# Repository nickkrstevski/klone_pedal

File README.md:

# klone_pedal

Overdrive guitar pedal

Created by Nicholas Krstevski <nick@atopile.com>

# Assembly BOM Table
| Description | Link |
|-------------|-------------|
| Audio Jack |

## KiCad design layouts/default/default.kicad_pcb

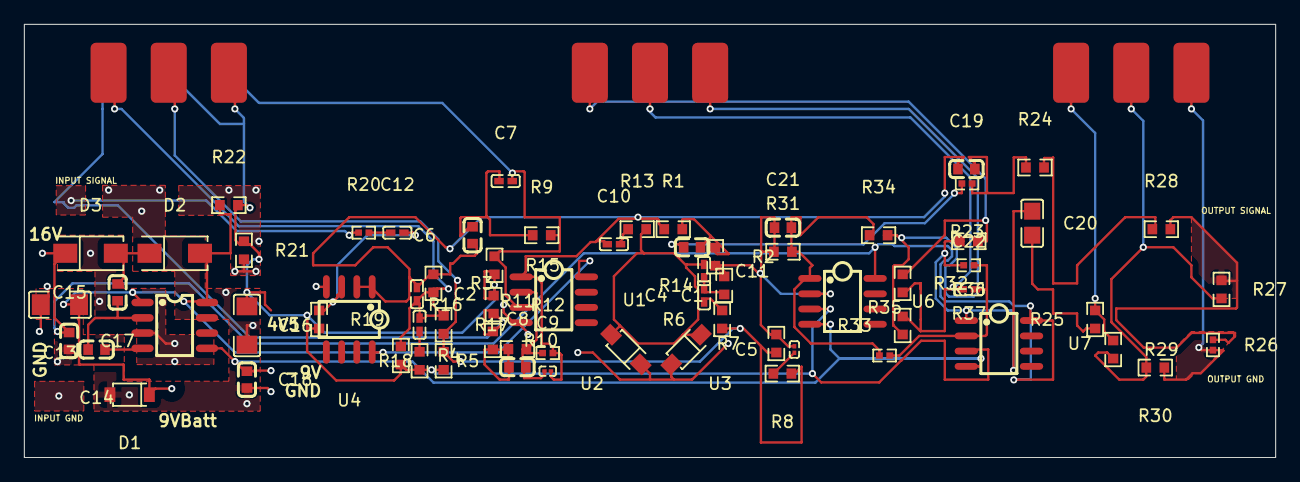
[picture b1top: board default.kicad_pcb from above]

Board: 2 copper layers, 104.0 x 36.0 mm, 73 parts (1 on the bottom side), 40 nets.

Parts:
C1, C6, C21: 100nF ±10% 50V X7R; C0603
C2, C7: 68nF ±5% 16V X7R; C0402
C3: 390nF ±10% 16V X5R; C0402
C4: 2.2nF ±10% 16V X7R; C0402
C5: 27nF ±10% 16V X5R; C0201
C8: 82nF ±10% 16V X7R; C0603
C9: 390pF ±5% 25V C0G; C0201
C10, C11: 1µF ±10% 25V X5R; C0402
C12: 100nF ±10% 16V X7R; C0402
C13, C16: 47µF ±20% 25V X5R; C1206
C14, C15, C17, C18: 1µF ±10% 50V X5R; C0603
C19: 4.7µF ±10% 16V X5R; C0603
C20: 4.7µF ±10% 50V X5R; C0805
C22: 3.9nF ±10% 50V X7R; C0402
D1: SOD-123_L2.7-W1.6-LS3.7-RD
D2, D3: SMA_L4.3-W2.5-LS5.0-RD
R1, R9, R15, R16, R17, R18, R21, R22, R27, R28, R29, R30, R31, R32, R33: 10kΩ ±1% 100mW; R0603
R2, R11: 15kΩ ±1% 100mW; R0603
R3: 5.1kΩ ±1% 100mW; R0603
R4: 1.5kΩ ±1% 100mW; R0603
R5, R13: 1kΩ ±1% 100mW; R0603
R6: 22kΩ ±1% 100mW; R0603
R7: 27kΩ ±1% 100mW; R0603
R8: 12kΩ ±1% 100mW; R0603
R10: 2kΩ ±1% 100mW; R0603
R12: 422kΩ ±1% 62.5mW; R0402
R14: 47kΩ ±1% 100mW; R0603
R19: 1MΩ ±1% 100mW; R0603
R20: 10kΩ ±1% 62.5mW; R0402
R23, R26, R35, R37: 100kΩ ±1% 62.5mW; R0402
R24, R25: 560Ω ±1% 100mW; R0603
R34: 1.8kΩ ±1% 100mW; R0603
R36: 4.7kΩ ±1% 100mW; R0603
U1, U4, U6, U7: SOIC-8_L5.0-W4.0-P1.27-LS6.0-BL
U2, U3: SOD-123FL_L2.7-W1.8-LS3.8-RD
U5, U8, U9, U11: D6_Potentiometer
U10: SOP-8_L4.9-W3.9-P1.27-LS6.0-BL

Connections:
-INPUT-1: R26.1, R27.1, R28.2
-P1INminus: C5.2, C21.1, R2.2, R7.2, R14.2, R31.1, U6.2
-gnd-0: C13.2, C16.2, C17.2, C18.2, D1.2, R21.2, U1.4, U2.1, U3.2, U4.4, U10.3
-gnd-1: C1.2, R23.2
-gnd-2: R26.2, R30.1, U9.3
-gnd-3: C18.1, U6.4, U7.4, U10.5
-hv-0: C13.1, D1.1, D2.2, R22.1, U1.8, U4.8, U10.1, U10.8
-hv-1: C16.1, R4.2, R5.2, R15.2, R16.2, R18.1, R19.2, R21.1, R22.2, U5.2, U6.3, U7.3, U8.3
-hv-2: C17.1, D3.1, U6.8, U7.8
-line: R24.2, R28.1
-output-0: C2.1, C6.1, C9.2, C10.1, C19.1, R1.1, R3.1, R12.2, U1.1, U4.1, U4.2
-output-1: C20.1, R36.2, R37.2, U7.1
-output-2: C21.2, R31.2, R34.1, R35.1, U6.1
CAPneg: C14.1, U10.4
CAPpos: C14.2, C15.1, U10.2
bypass-tap: C19.2, R23.1, R24.1
cathode: C15.2, D2.1, D3.2
gain_stage-P1INminus: C8.2, C9.1, R11.2, R12.1, U1.2
gain_stage-P1INplus: C7.2, R9.2, R15.1, U1.3, U5.1
gain_stage-line: C1.1, R1.2, R2.1
gain_stage-net-0: C4.1, R6.2
gain_stage-net-1: C5.1, R8.2
gain_stage-net-2: C3.2, R5.1
gain_stage-net-3: C6.2, C7.1, R9.1
gain_stage-net-4: C8.1, R10.2, R11.1
gain_stage-net-5: C10.2, R13.1
gain_stage-resistors_ifs[0]: C2.2, C3.1, R3.2, R4.1, R17.1, U8.1
gain_stage-resistors_ifs[1]: R10.1, R16.1, U5.3
gain_stage-tap-0: C11.1, R13.2, U2.2, U3.1
gain_stage-tap-1: C4.2, C11.2, R14.1
gain_stage-wiper: R6.1, R7.1, R8.1, R17.2, R18.2, U8.2
input_stage-P1INplus: C12.2, R19.1, U4.3
input_stage-net: C12.1, R20.2
output_stage-gnd: R27.2, R29.2, R30.2, U9.2
output_stage-net: C20.2, R25.1
output_stage-resistors_ifs[0]: R25.2, R29.1, U9.1
tone_control-P1INminus: C22.2, R35.2, R37.1, U7.2
tone_control-resistors_ifs[0]: R32.1, R36.1, U11.1
tone_control-resistors_ifs[1]: R33.1, R34.2, U11.3
tone_control-wiper: C22.1, R32.2, R33.2, U11.2

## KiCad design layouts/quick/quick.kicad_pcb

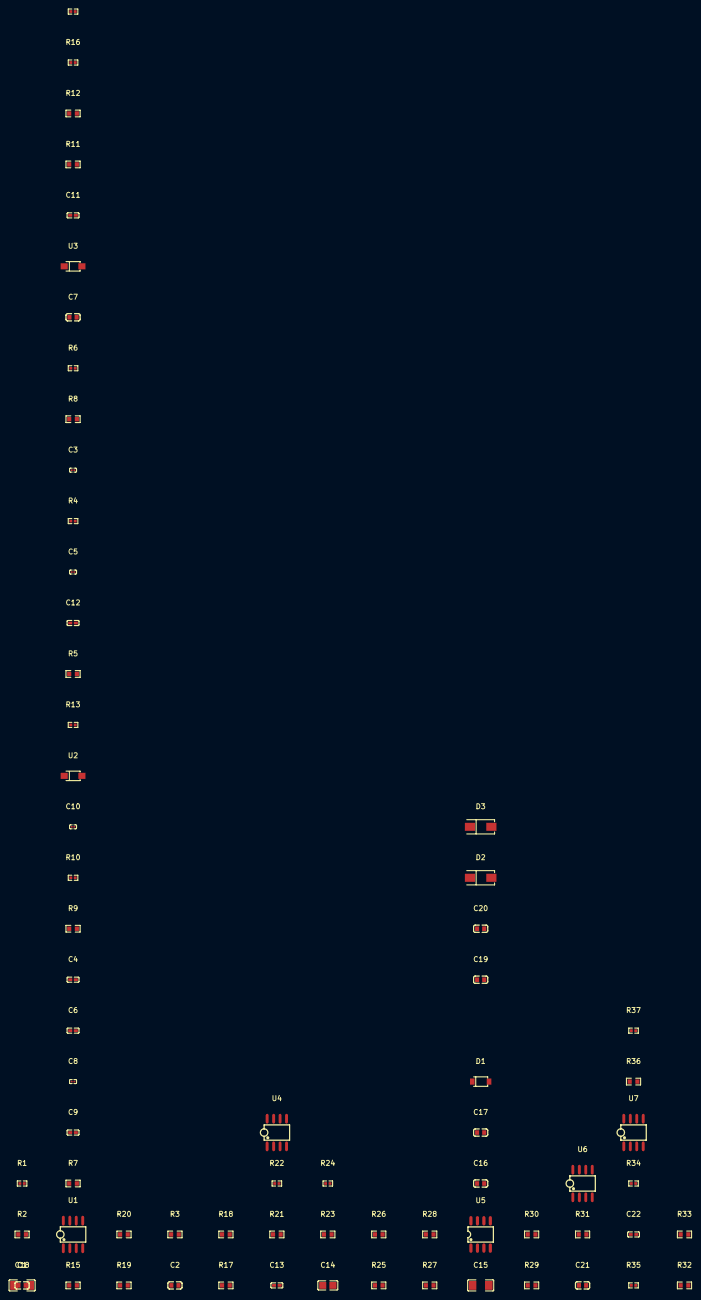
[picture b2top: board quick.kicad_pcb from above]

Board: 2 copper layers, 69 parts (0 on the bottom side), 42 nets, no tracks yet.

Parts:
C1: 4.7µF ±10% 16V X5R; C0603-bd72f6
C2, C7, C21: 100nF ±10% 50V X7R; C0603-bd72f6
C3, C8: 68nF ±10% 16V X5R; C0201-a4ec75
C4: 390nF ±10% 16V X5R; C0402-b3ef17
C5: 2.2nF ±10% 25V X7R; C0201-a4ec75
C6: 27nF ±10% 16V X7R; C0402-b3ef17
C9: 82nF ±10% 16V X7R; C0402-b3ef17
C10: 390pF ±5% 25V C0G; C0201-a4ec75
C11, C12: 1µF ±10% 25V X5R; C0402-b3ef17
C13: 100nF ±10% 16V X7R; C0402-b3ef17
C14: 4.7µF ±10% 50V X5R; C0805-3b2e55
C15, C18: 47µF ±20% 25V X5R; C1206-f0a137
C16, C17, C19, C20: 1µF ±10% 50V X5R; C0603-bd72f6
C22: 3.9nF ±10% 50V X7R; C0402-b3ef17
D1: SOD-123_L2.7-W1.6-LS3.7-RD-30fb4b
D2, D3: SMA_L4.3-W2.5-LS5.0-RD-e683d9
R1, R24, R35, R37: 100kΩ ±1% 62.5mW; R0402-56259e
R2, R23: 560Ω ±1% 100mW; R0603-ebcab9
R3, R7, R15, R17, R18, R19, R20, R25, R26, R27, R28, R29, R30, R31, R32, R33: 1kΩ ±1% 100mW; R0603-ebcab9
R4, R13: 15kΩ ±1% 62.5mW; R0402-56259e
R5: 5.1kΩ ±1% 100mW; R0603-ebcab9
R6: 1.5kΩ ±1% 62.5mW; R0402-56259e
R8: 22kΩ ±1% 100mW; R0603-ebcab9
R9: 27kΩ ±1% 100mW; R0603-ebcab9
R10: 12kΩ ±1% 62.5mW; R0402-56259e
R11: 10kΩ ±1% 100mW; R0603-ebcab9
R12: 2kΩ ±1% 100mW; R0603-ebcab9
R14: 422kΩ ±1% 62.5mW; R0402-56259e
R16: 47kΩ ±1% 62.5mW; R0402-56259e
R21: 1MΩ ±1% 100mW; R0603-ebcab9
R22: 10kΩ ±1% 62.5mW; R0402-56259e
R34: 1.8kΩ ±1% 62.5mW; R0402-56259e
R36: 4.7kΩ ±1% 100mW; R0603-ebcab9
U1, U4, U6, U7: SOIC-8_L5.0-W4.0-P1.27-LS6.0-BL-294f77
U2, U3: SOD-123FL_L2.7-W1.8-LS3.8-RD-0c8348
U5: SOP-8_L4.9-W3.9-P1.27-LS6.0-BL-0d1ac6

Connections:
CAPminus: C16.1, U5.4
CAPplus: C16.2, C17.1, U5.2
INPUT: R24.1, R25.1, R26.2
bypass-tap: C1.2, R1.1, R2.1
gain_stage-P1INminus: C9.2, C10.1, R13.2, R14.1, U1.2
gain_stage-P1INplus: C8.2, R11.2, R17.1, U1.3
gain_stage-cathode: C12.1, R15.2, U2.2, U3.1
gain_stage-line: C7.2, C8.1, R3.1, R11.1
gain_stage-line-1: C2.1, R3.2, R4.1
gain_stage-net: C6.1, R10.2
gain_stage-net-1: C4.2, R7.1
gain_stage-net-2: C5.1, R8.2
gain_stage-net-3: C11.2, R15.1
gain_stage-net-4: C9.1, R12.2, R13.1
gain_stage-output: C7.1, C10.2, C11.1, R14.2, U1.1
gain_stage-resistors_ifs[0]: C3.2, C4.1, R5.2, R6.1, R19.1
gain_stage-resistors_ifs[1]: R12.1, R18.1
gain_stage-tap: C5.2, C12.2, R16.1
gain_stage-wiper: R8.1, R9.1, R10.1, R19.2, R20.2
gnd-1: R24.2, R28.1
gnd-2: C15.2, C18.2, C19.2, C20.2, D1.2, R29.2, U1.4, U2.1, U3.2, U4.4, U5.3
gnd-3: C20.1, U5.5, U6.4, U7.4
hv: C15.1, D1.1, D2.2, R30.1, U1.8, U4.8, U5.1, U5.8
hv-1: C18.1, R6.2, R7.2, R17.2, R18.2, R20.1, R21.2, R29.1, R30.2, U6.3, U7.3
hv-2: C19.1, D3.1, U6.8, U7.8
input_stage-P1INplus: C13.2, R21.1, U4.3
input_stage-net: C13.1, R22.2
input_stage.input_buffer_opamp-P1INminus: U4.1, U4.2
line: R2.2, R26.1
line-1: C1.1, C3.1, R5.1
line-2: C6.2, R4.2, R9.2, R16.2
output: C21.2, R31.2, R34.1, R35.1, U6.1
output-1: C14.1, R36.2, R37.2, U7.1
output_stage-gnd: R25.2, R27.2, R28.2
output_stage-net: C14.2, R23.1
output_stage-resistors_ifs[0]: R23.2, R27.1
power_supply-cathode: C17.2, D2.1, D3.2
summing_opamp-P1INminus: C21.1, R31.1, U6.2
tone_control-P1INminus: C22.2, R35.2, R37.1, U7.2
tone_control-resistors_ifs[0]: R32.1, R36.1
tone_control-resistors_ifs[1]: R33.1, R34.2
tone_control-wiper: C22.1, R32.2, R33.2

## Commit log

2025-05-11 power supply and input buffer
2025-05-12 gain stage implemented
2025-05-12 summing stage and bug fix
2025-05-12 added tone stage
2025-05-12 bypass mode added
2025-05-15 Added plugin to show atopile_address on layout
2025-05-17 dump
2025-05-18 rearranged, not building. Plugin fixed
2025-05-18 adding icon
2025-05-19 building
2025-05-20 layout floorplan complete
2025-05-22 fancy layout
2025-05-28 layout updates
2025-06-20 building on latest
2025-06-20 ripping through layout
2025-06-26 fighting off the rats
2025-06-30 layout nearly complete
2025-07-09 update layout with test pads
